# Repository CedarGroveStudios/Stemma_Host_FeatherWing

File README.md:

# UNTESTED: Stemma Host FeatherWing

### _A Stemma UART/I2C FeatherWing interface for use with a host MCU Feather board._

The Stemma Host FeatherWing is a single Stemma or StemmaQT interface, compatible with the Adafruit Feather format. It is designed for use with a Feather MCU board such as the Feather M4 Express and will selectively communicate via UART (RX/TX) or I2C (SDA/SCL). The Stemma connector power is provided by the host Feather and is selectable for either 3 volts or ~5 volts. Stemma 2.0mm and Stemma-QT 1.0mm connector types are supported. 

For use ONLY with Feather MCU boards that provide at least a 3.3-volt power source. USB or battery power is needed for Stemma ~5-volt signals.

OSH Park project: https://oshpark.com/shared_projects/8VwYkydw

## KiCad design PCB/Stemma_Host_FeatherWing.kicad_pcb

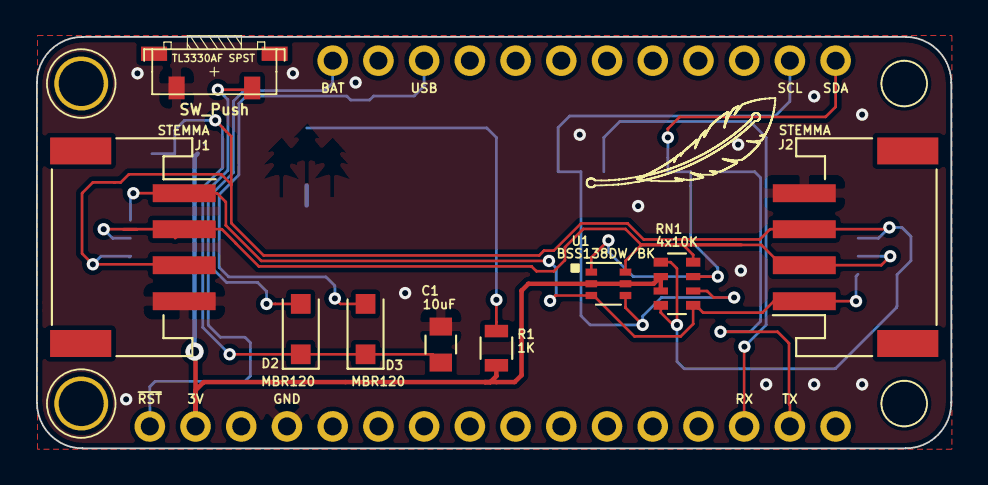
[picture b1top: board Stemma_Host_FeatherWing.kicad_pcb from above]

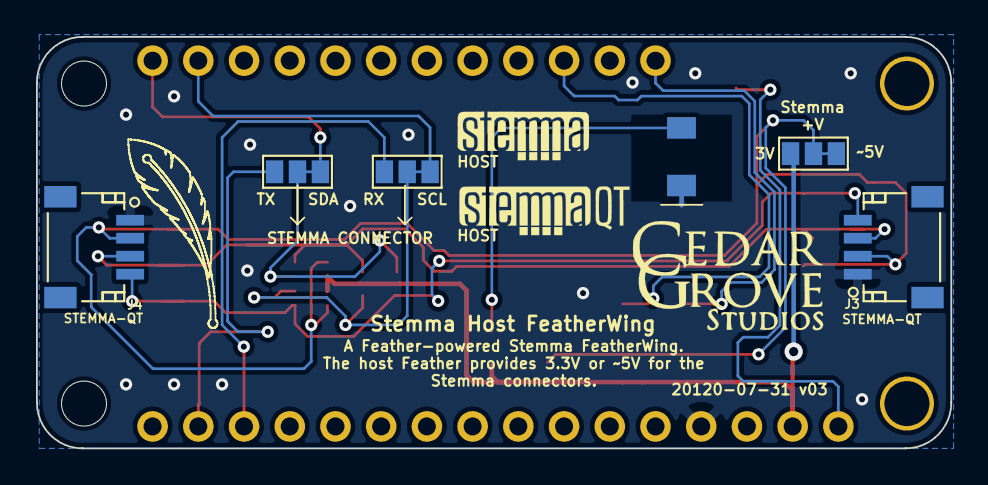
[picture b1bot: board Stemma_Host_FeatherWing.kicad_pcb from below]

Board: 2 copper layers, 50.8 x 22.9 mm, 16 parts (5 on the bottom side), 13 nets.

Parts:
C1: 10uF; C_0805
D1: GRN; Cedar_Grove_logo_lighted
D2, D3: MBR120; D_SOD-123F
J1, J2: STEMMA; JST_PH_S4B-PH-SM4-TB_04x2.00mm_Angled
J3, J4: STEMMA-QT; JST_SH_SM04B-SRSS-TB_04x1.00mm_Angled
JMP1: SCL_RX; GS3
JMP2: SDA_TX; GS3
JMP3: STEMMA_TYPE; GS3
M1: Feather_M4_Express; Adafruit_Feather_M4_Express_bare
R1: 1K; R_0805
RN1: 4x10K; R_Array_Convex_4x0603
SW1: SW_Push; TL3330AF_SPST_BUTTON_RT-ANGLE_7.8mm_2.5mm_2.5mm
U1: BSS138DW/BK; SOT-363_SC-70-6

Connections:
+3V3: JMP3.1, M1.2, R1.1, RN1.2, RN1.3, U1.2, U1.5
/+V: C1.1, D2.1, D3.1, J1.3, J2.3, J3.2, J4.2, JMP3.2, JMP3.3, RN1.1, RN1.4
/BAT: D2.2, M1.17
/RX: JMP1.3, M1.14
/SCL: JMP1.1, JMP1.2, M1.27, RN1.6, U1.4
/SDA: JMP2.1, JMP2.2, M1.28, RN1.7, U1.1
/STEMMA_SCL: J1.1, J2.1, J3.4, J4.4, RN1.5, U1.3
/STEMMA_SDA: J1.2, J2.2, J3.3, J4.3, RN1.8, U1.6
/TX: JMP2.3, M1.15
/USB: D3.2, M1.19
/~RST: M1.1, SW1.2
GND: C1.2, D1.1, J1.4, J2.4, J3.1, J4.1, M1.4, SW1.1
unnamed: D1.2, R1.2

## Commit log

2019-11-27 initial repo load
2019-11-27 update with initial design
2019-11-27 update renderings
2019-11-27 update impl chart
2019-11-27 update design
2019-12-10 PCB version update
2020-07-31 correct stemma-qt pinout
2021-03-04 remove duplicate graphics
2021-07-12 update documentation
